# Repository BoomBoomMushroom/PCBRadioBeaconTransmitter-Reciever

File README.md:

# PCB Beacon Radio Transmitter and Reciever

My pcb contains both a transmitter and reciever! 

## Schematic

## PCB

## Features
- Low power design! 3V operating voltage
- Can be tuned with the potentiometer
- Has a Colpitts-esque oscillator
- Built in antennas

## BOM
- 2 	Battery holder
- 1 	10uF Capacitor
- 1	  PNP Transistor
- 1	  NPN Transistor
- 1	  4.7k Resistor
- 1	  47k Resistor
- 2 	220 Resistor
- 1 	Potentiometer
- 1 	LED

Made by `@Laney` on slack :D

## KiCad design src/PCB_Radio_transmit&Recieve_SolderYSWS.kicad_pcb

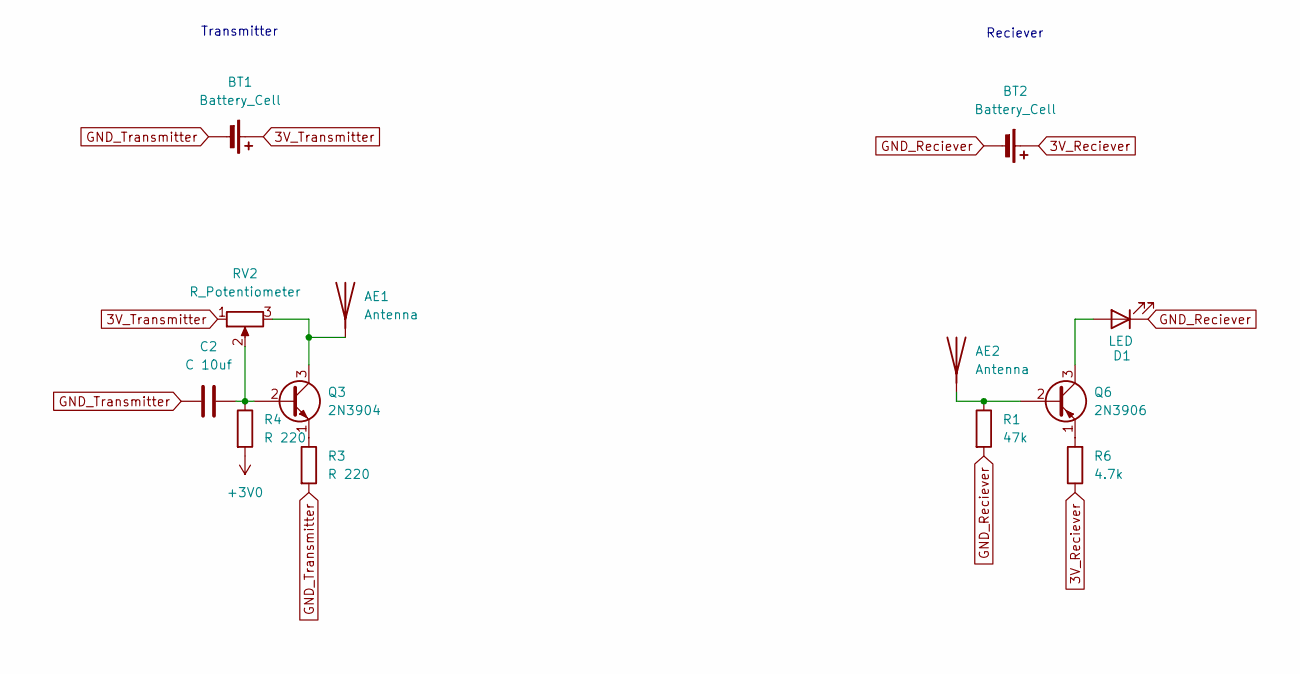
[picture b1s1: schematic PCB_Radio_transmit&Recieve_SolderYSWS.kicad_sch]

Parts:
AE1, AE2: Antenna; Texas_SWRA117D_2.4GHz_Right
BT1, BT2: Battery_Cell; BatteryHolder_Multicomp_BC-2001_1x2032
C2: C 10uf; CP_Radial_D6.3mm_P2.50mm
D1: LED; LED_D3.0mm
Q3: 2N3904; TO-92_Inline
Q6: 2N3906; TO-92_Inline
R1: 47k; R_Axial_DIN0204_L3.6mm_D1.6mm_P5.08mm_Horizontal
R3, R4: R 220; R_Axial_DIN0204_L3.6mm_D1.6mm_P5.08mm_Horizontal
R6: 4.7k; R_Axial_DIN0204_L3.6mm_D1.6mm_P5.08mm_Horizontal
RV2: R_Potentiometer; Potentiometer_Bourns_3386P_Vertical

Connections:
3V_Reciever: BT2.1 (+), R6.1
3V_Transmitter: BT1.1 (+), RV2.1
+3V0: R4.2
GND_Reciever: BT2.2 (-), D1.1 (K), R1.2
GND_Transmitter: BT1.2 (-), C2.1, R3.2
unnamed: AE1.1 (A), Q3.3 (C), RV2.3
unnamed: AE2.1 (A), Q6.2 (B), R1.1
unnamed: D1.2 (A), Q6.3 (C)
unnamed: C2.2, Q3.2 (B), R4.1, RV2.2
unnamed: Q3.1 (E), R3.1
unnamed: Q6.1 (E), R6.2

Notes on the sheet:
Reciever
Transmitter

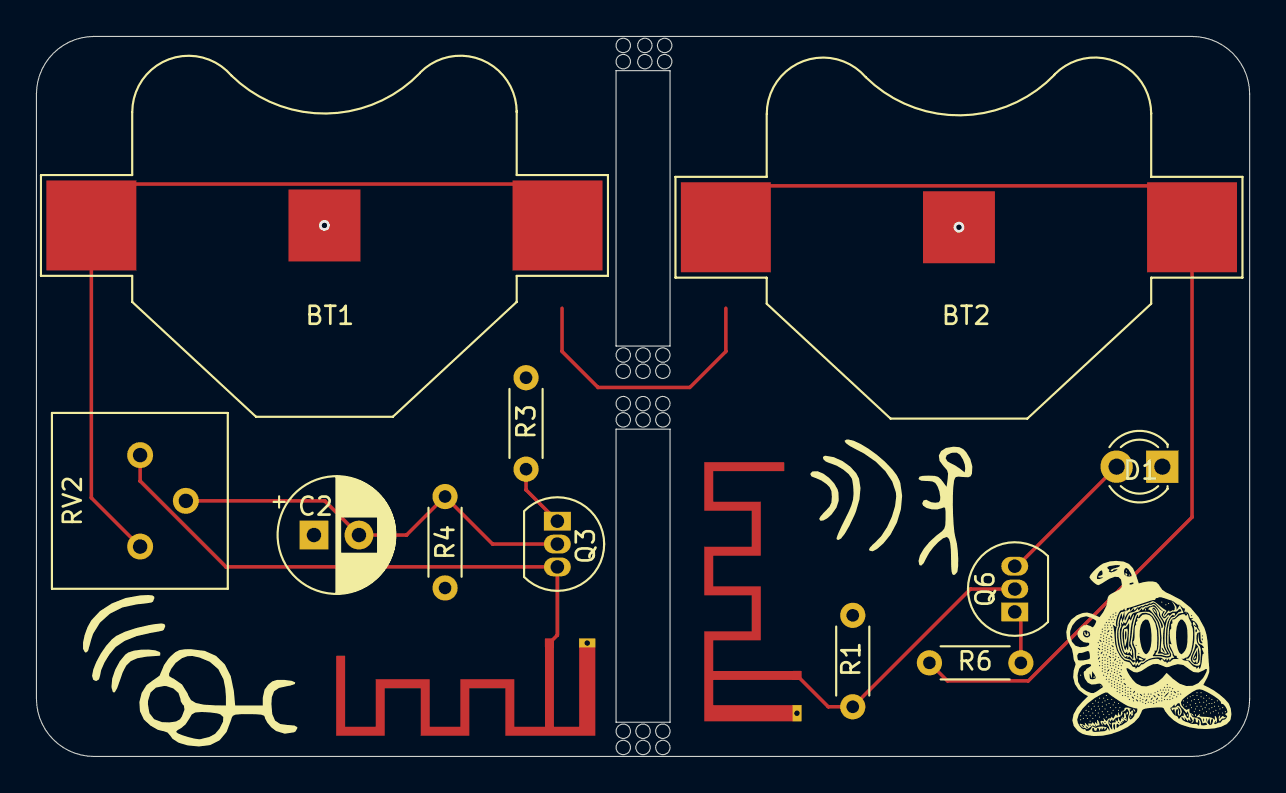
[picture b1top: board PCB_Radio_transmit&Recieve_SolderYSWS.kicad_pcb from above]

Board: 2 copper layers, 67.4 x 40.0 mm, 13 parts (0 on the bottom side), 10 nets.

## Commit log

2025-05-02 added stuff
2025-05-02 updated!
